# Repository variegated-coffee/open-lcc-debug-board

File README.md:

# Open LCC Debug Board

Schematics and PCB files for the Open LCC debug board. Licensed under the CERN OHL-P license.

The Debug Board exposes SWD, JTAG, USB and Reset/GPIO0/Bootsel for the RP2040 and ESP32-S3 on the Open LCC Main Board.

It also has an optional boost converter to provide 12V instead of 5V as VIN to the Open LCC Main board. When using the color TFT, this doesn't matter at all. When using the OLED, the OLED is dimmer when powered using 5V. You probably don't need this boost converter.

## Disclaimer

Anything you do with this, you do at your own risk. Components have been fried already during the course of this project. Your machine uses both line voltage power, high pressured hot water, steam and other dangerous components. Risks include but are not limited to, damaging the machine, personal injury, property damage and summoning dead Cthulhu from his sleep at R'lyeh.

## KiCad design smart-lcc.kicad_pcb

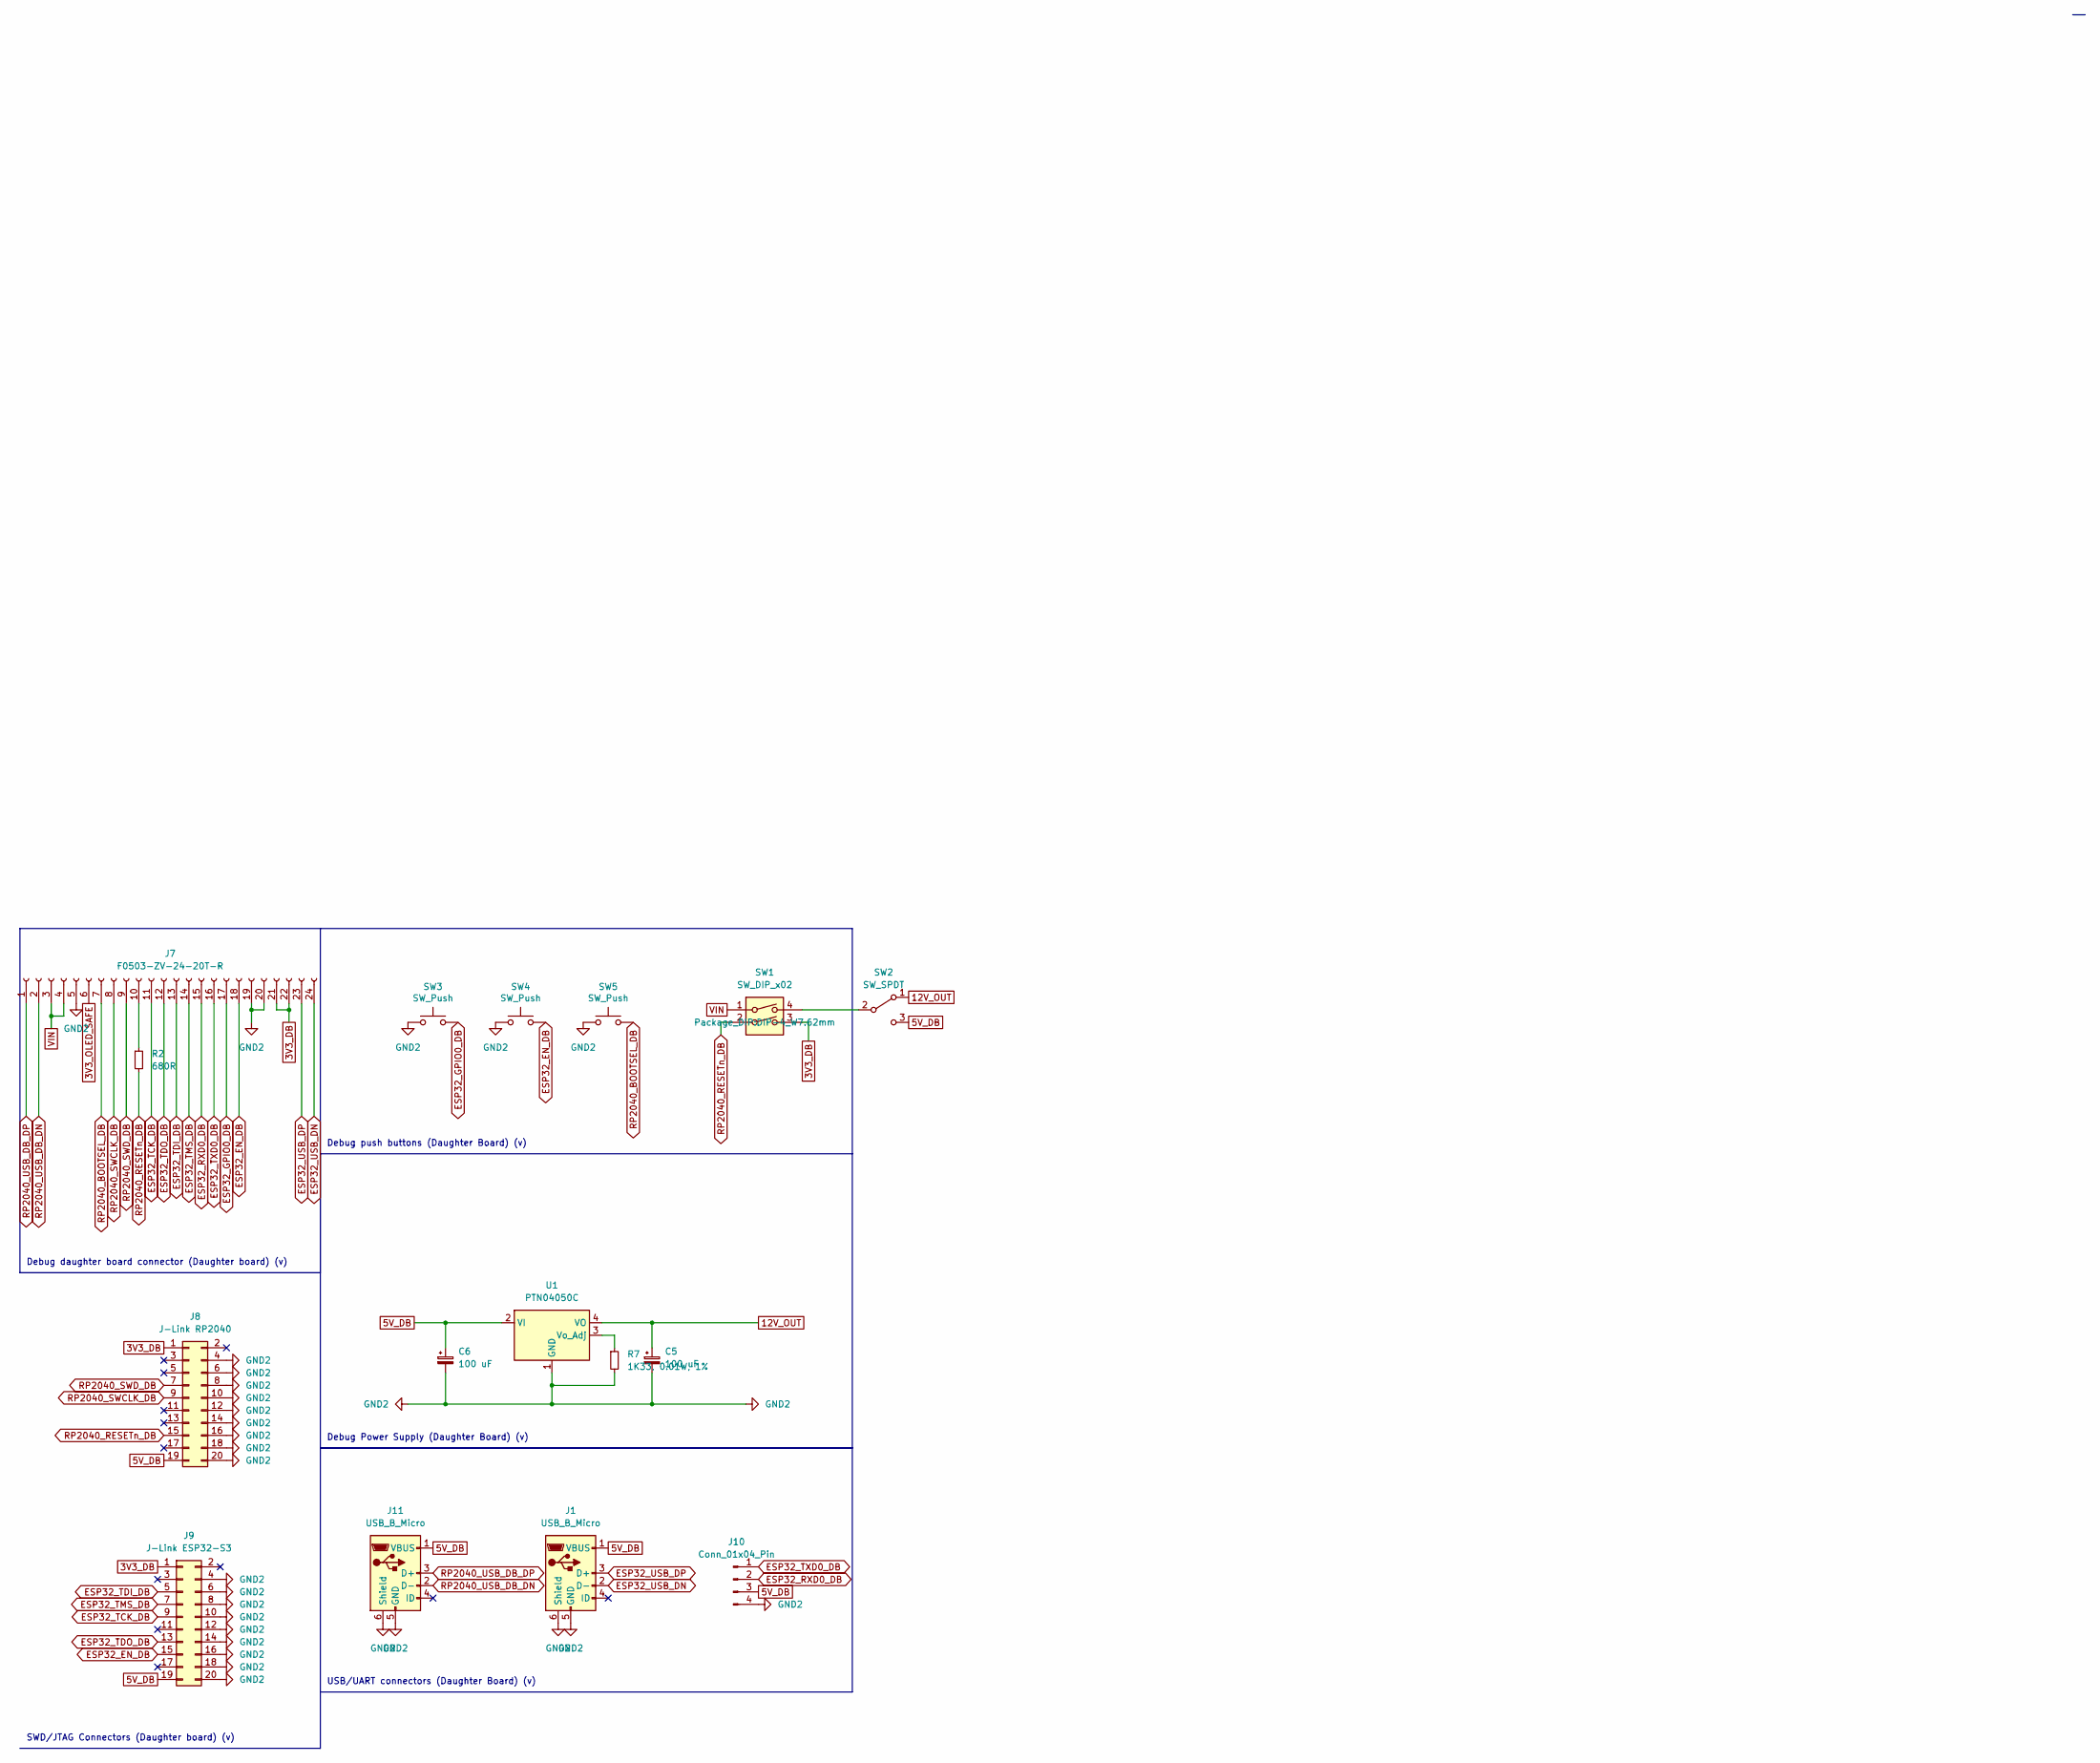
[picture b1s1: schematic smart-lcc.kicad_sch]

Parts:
C5, C6: 100 uF; CP_Radial_D7.5mm_P2.50mm
J1, J11: USB_B_Micro; USB_Micro-B_Molex-105133-0001; LCSC C586226
J7: F0503-ZV-24-20T-R; FPC_24; JLCPCB Basic N
J8: J-Link RP2040; IDC-Header_2x10_P2.54mm_Vertical
J9: J-Link ESP32-S3; IDC-Header_2x10_P2.54mm_Vertical
J10: Conn_01x04_Pin; PinHeader_1x04_P2.54mm_Vertical
R2: 680R; R_Axial_DIN0204_L3.6mm_D1.6mm_P7.62mm_Horizontal
R7: 1K33, 0.01W, 1%; R_Axial_DIN0204_L3.6mm_D1.6mm_P7.62mm_Horizontal
SW1: SW_DIP_x02; DIP-4_W7.62mm
SW2: SW_SPDT; PinHeader_1x03_P2.54mm_Vertical
SW3, SW4, SW5: SW_Push; ADTSMW65
U1: PTN04050C; CONV_PTN04050CAD

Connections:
3V3_DB: J7.21, J7.22, J8.1, J9.1, SW1.3
3V3_OLED_SAFE: J7.6
5V_DB: C6.1, J1.1 (VBUS), J8.19, J9.19, J10.3, J11.1 (VBUS), SW2.3 (C), U1.2 (VI)
12V_OUT: C5.1, SW2.1 (A), U1.4 (VO)
ESP32_EN_DB: J7.18, J9.15, SW4.2
ESP32_GPIO0_DB: J7.17, SW3.2
ESP32_RXD0_DB: J7.15, J10.2
ESP32_TCK_DB: J7.11, J9.9
ESP32_TDI_DB: J7.13, J9.5
ESP32_TDO_DB: J7.12, J9.13
ESP32_TMS_DB: J7.14, J9.7
ESP32_TXD0_DB: J7.16, J10.1
ESP32_USB_DN: J1.2 (D-), J7.24
ESP32_USB_DP: J1.3 (D+), J7.23
GND2: C5.2, C6.2, J1.5 (GND), J1.6 (Shield), J7.5, J7.19, J7.20, J8.4, J8.6, J8.8, J8.10, J8.12, J8.14, J8.16, J8.18, J8.20, J9.4, J9.6, J9.8, J9.10, J9.12, J9.14, J9.16, J9.18, J9.20, J10.4, J11.5 (GND), J11.6 (Shield), R7.2, SW3.1, SW4.1, SW5.1, U1.1 (GND)
unnamed: J7.10, R2.1
unnamed: SW1.4, SW2.2 (B)
unnamed: R7.1, U1.3 (Vo_Adj)
RP2040_BOOTSEL_DB: J7.7, SW5.2
RP2040_RESETn_DB: J8.15, R2.2, SW1.2
RP2040_SWCLK_DB: J7.8, J8.9
RP2040_SWD_DB: J7.9, J8.7
RP2040_USB_DB_DN: J7.2, J11.2 (D-)
RP2040_USB_DB_DP: J7.1, J11.3 (D+)
VIN: J7.3, J7.4, SW1.1

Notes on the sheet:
Debug daughter board connector (Daughter board) (v)
SWD/JTAG Connectors (Daughter board) (v)
USB/UART connectors (Daughter Board) (v)
Debug push buttons (Daughter Board) (v)
Debug Power Supply (Daughter Board) (v)

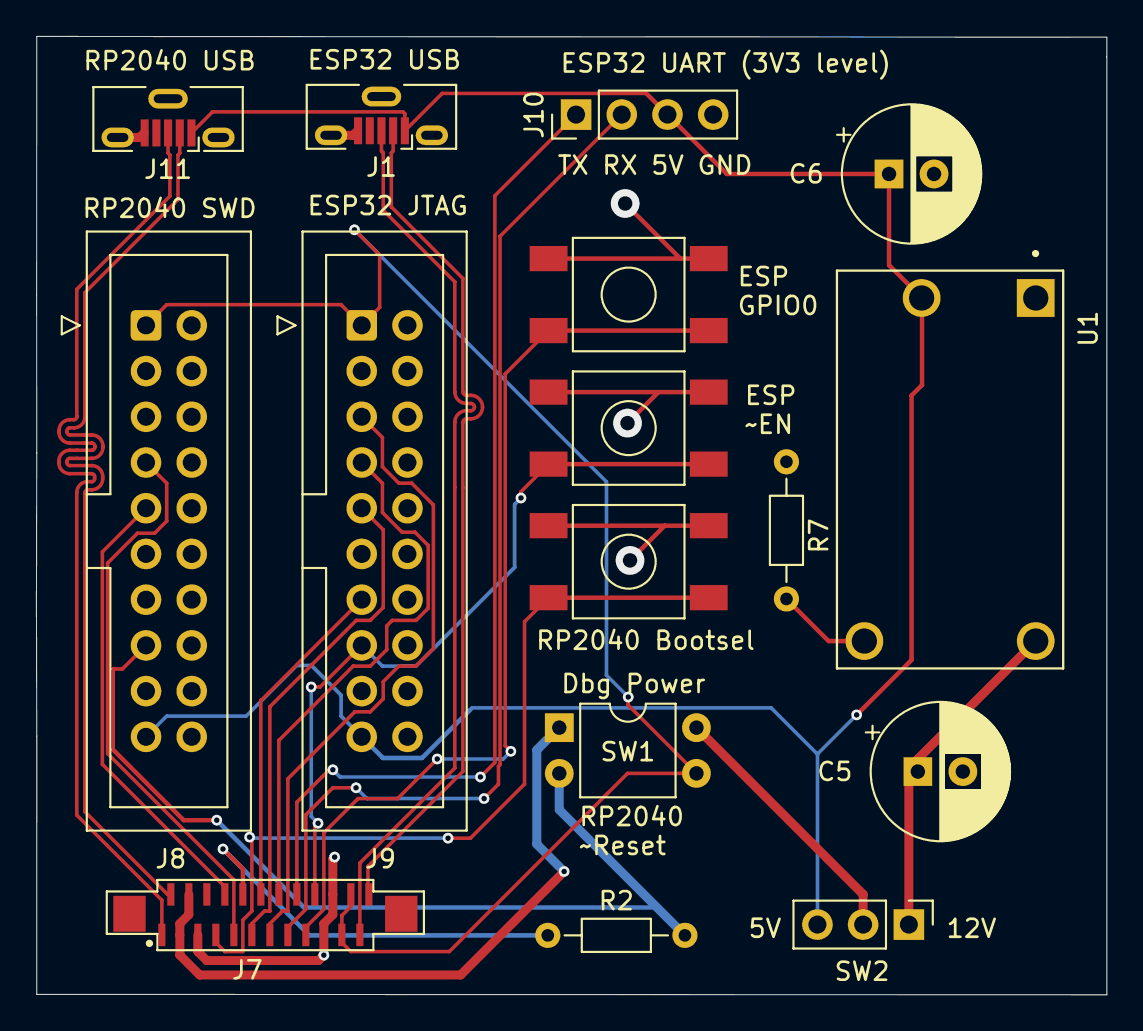
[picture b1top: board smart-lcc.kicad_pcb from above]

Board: 2 copper layers, 59.5 x 53.2 mm, 16 parts (0 on the bottom side), 24 nets.

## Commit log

2024-02-24 Initial import
2024-02-24 Added manufacturing data
2024-02-24 Manufacturing instructions
2024-02-24 Added Readme and License
2024-02-25 Updated with value for R2 resistor

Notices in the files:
smart-lcc.kicad_pcb:
Licensed under CERN-OHL-P v2
